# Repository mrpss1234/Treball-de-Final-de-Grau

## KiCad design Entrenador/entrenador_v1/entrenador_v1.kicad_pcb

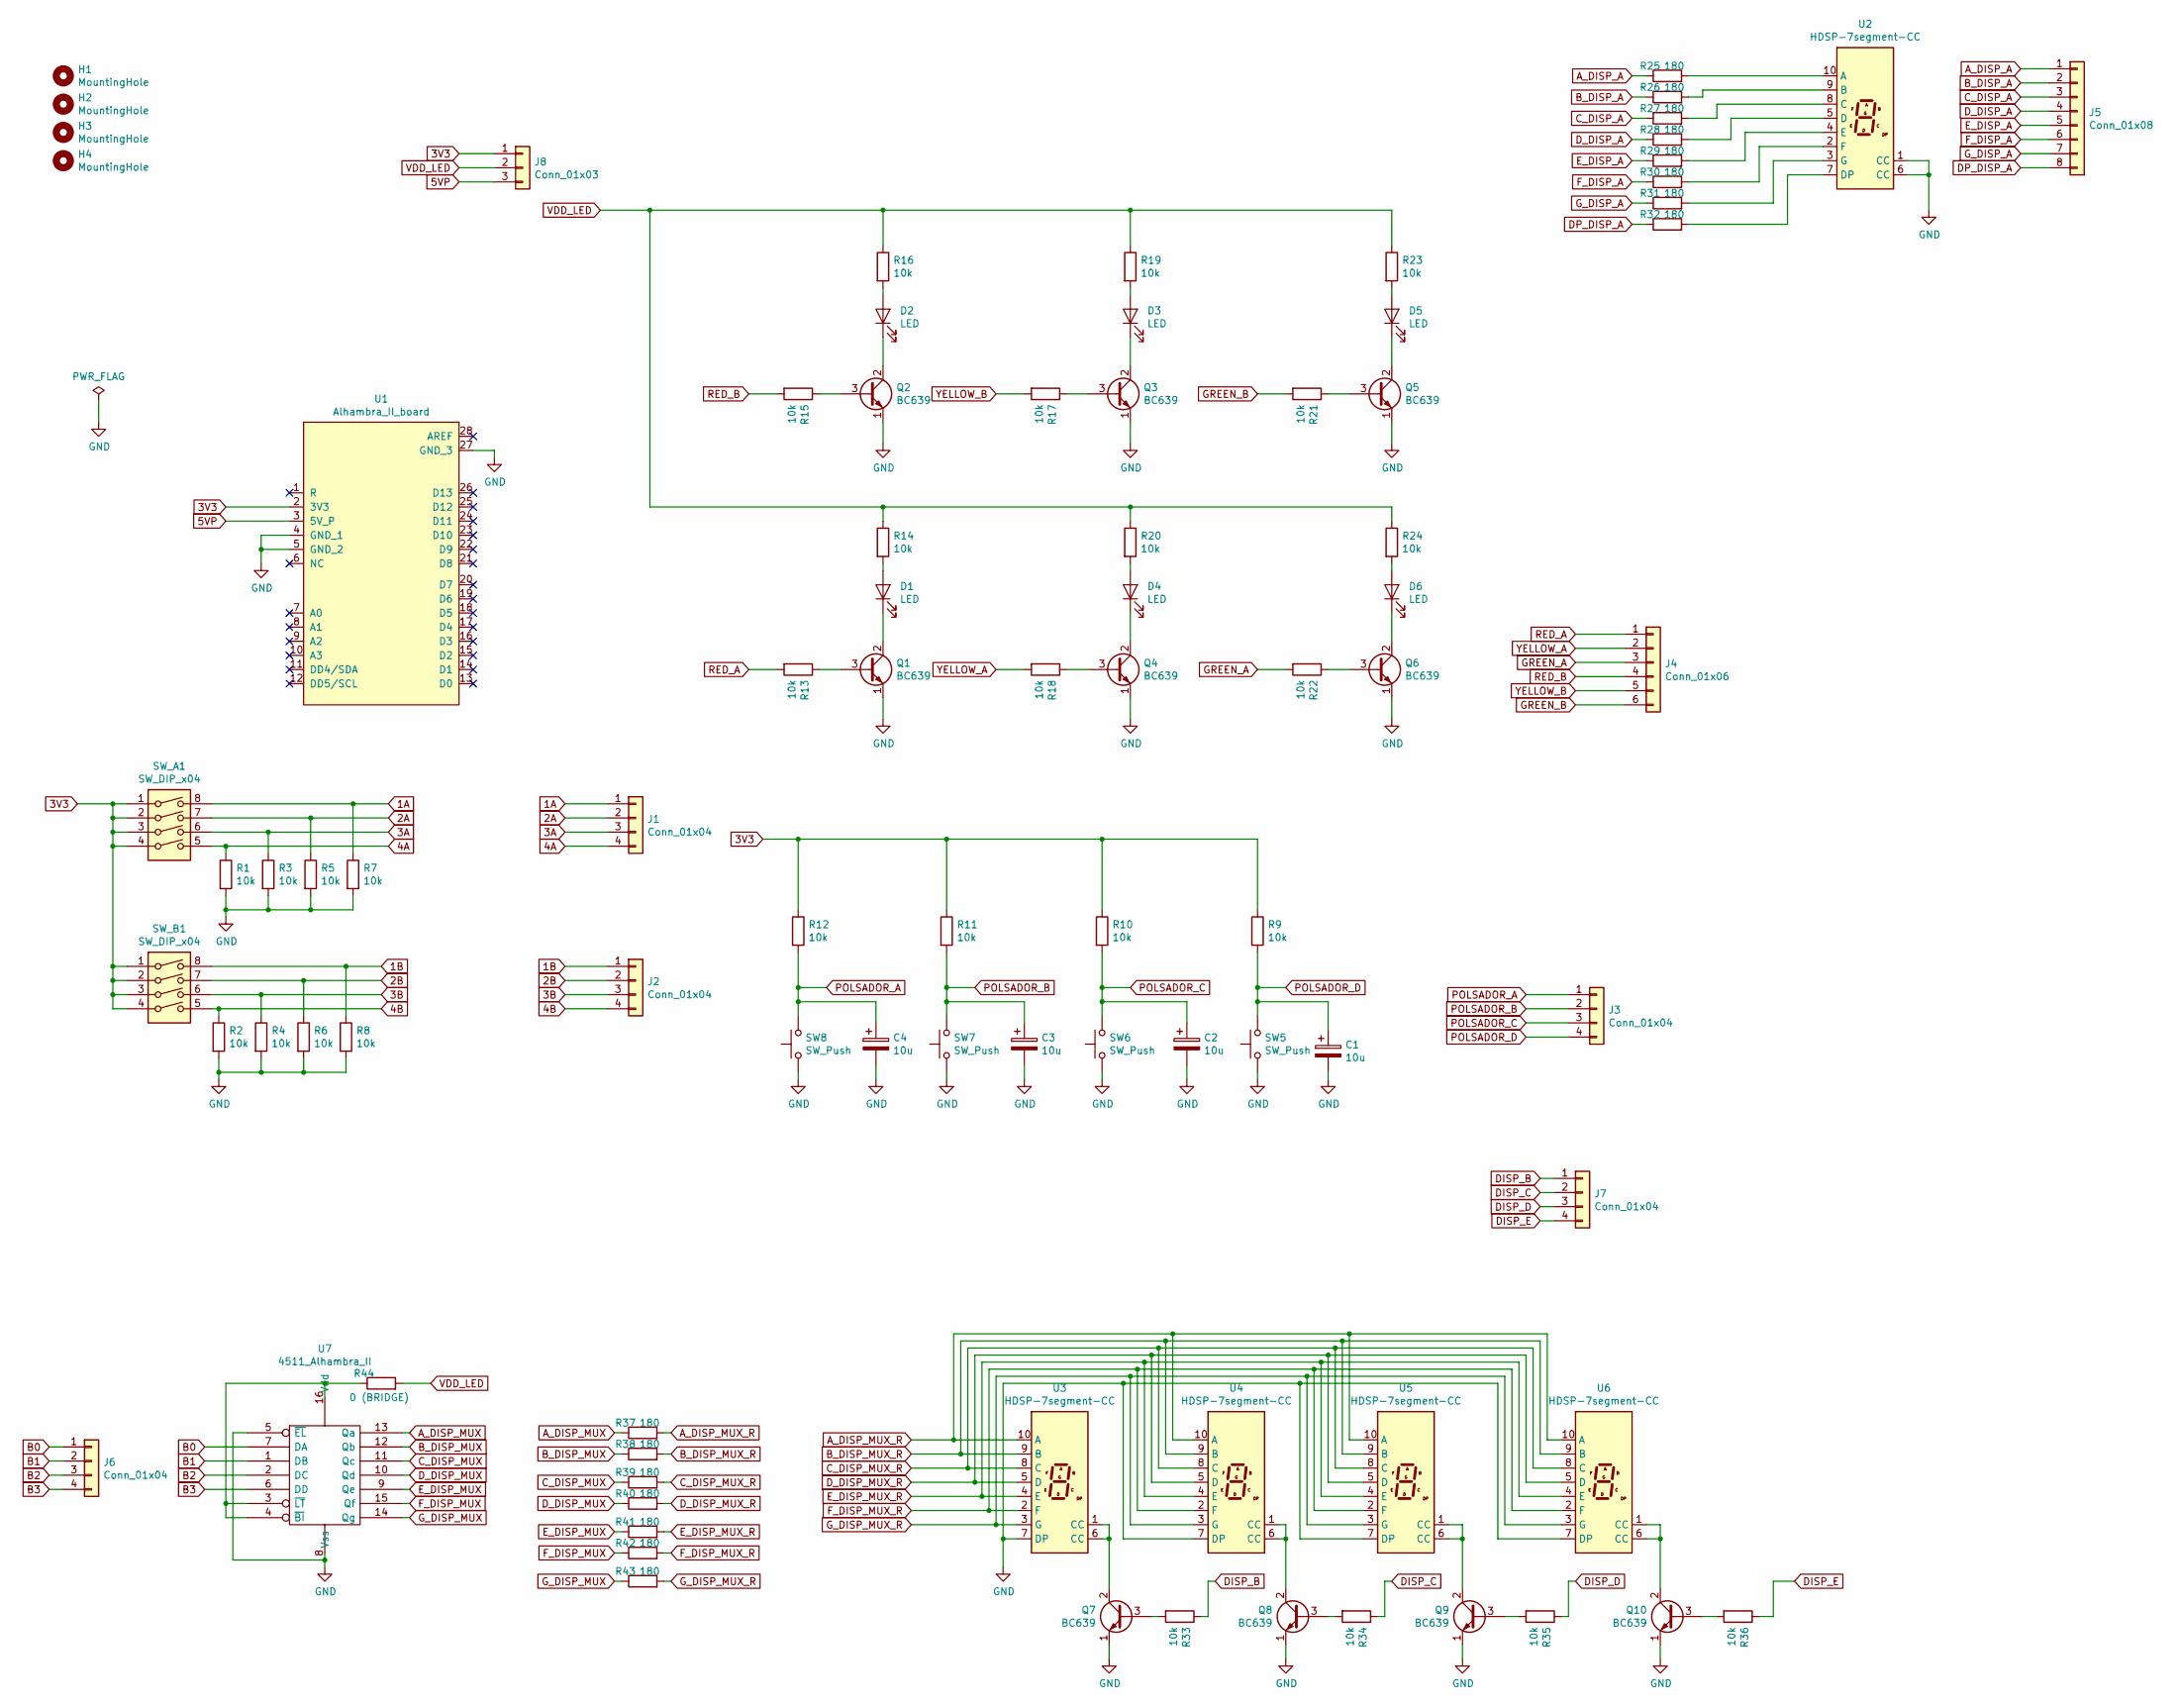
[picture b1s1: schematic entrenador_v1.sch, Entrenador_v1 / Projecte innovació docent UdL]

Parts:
C1, C2, C3, C4: 10u; CP_Radial_D5.0mm_P2.50mm
D1, D2, D3, D4, D5, D6: LED; LED_D3.0mm_Alhambra_II
H1, H2, H3, H4: MountingHole; MountingHole_4mm
J1, J2, J3, J6, J7: Conn_01x04; PinSocket_1x04_P2.54mm_Vertical_Alhambra_II
J4: Conn_01x06; PinSocket_1x06_P2.54mm_Vertical_Alhambra_II
J5: Conn_01x08; PinSocket_1x08_P2.54mm_Vertical_Alhambra_II
J8: Conn_01x03; PinHeader_1x03_P2.54mm_Vertical_Alhambra_II
Q1, Q2, Q3, Q4, Q5, Q6, Q7, Q8, Q9, Q10: BC639; TO-92L_Inline_Wide_Alhambra_II
R1, R2, R3, R4, R5, R6, R7, R8, R9, R10, R11, R12, R13, R14, R15, R16, R17, R18, R19, R20, R21, R22, R23, R24, R33, R34, R35, R36: 10k; R_Axial_Alhambra_II
R25, R26, R27, R28, R29, R30, R31, R32, R37, R38, R39, R40, R41, R42, R43: 180; R_Axial_Alhambra_II
R44: 0 (BRIDGE); R_Axial_Alhambra_II
SW5, SW6, SW7, SW8: SW_Push; PUSH_Button_Alhambra_II
SW_A1: SW_DIP_x04; DIP_SWITCH_4P_Alhambra_II
SW_B1: SW_DIP_x04; DIP_SWITCH_4P_Alhambra_II
U1: Alhambra_II_board; Alhambra_II_UdL_v2
U2, U3, U4, U5, U6: HDSP-7segment-CC; HDSP_7seg_Alhambra_II
U7: 4511_Alhambra_II; DIP-16_W7.62mm_Socket_LongPads

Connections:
1A: J1.1, R7.1, SW_A1.8
1B: J2.1, R8.1, SW_B1.8
2A: J1.2, R5.1, SW_A1.7
2B: J2.2, R6.1, SW_B1.7
3A: J1.3, R3.1, SW_A1.6
3B: J2.3, R4.1, SW_B1.6
3V3: J8.1, R9.1, R10.1, R11.1, R12.1, SW_A1.1, SW_A1.2, SW_A1.3, SW_A1.4, SW_B1.1, SW_B1.2, SW_B1.3, SW_B1.4, U1.2 (3V3)
4A: J1.4, R1.1, SW_A1.5
4B: J2.4, R2.1, SW_B1.5
5VP: J8.3, U1.3 (5V_P)
A_DISP_A: J5.1, R25.1
A_DISP_MUX: R37.1, U7.13 (Qa)
A_DISP_MUX_R: R37.2, U3.10 (A), U4.10 (A), U5.10 (A), U6.10 (A)
B0: J6.1, U7.7 (DA)
B1: J6.2, U7.1 (DB)
B2: J6.3, U7.2 (DC)
B3: J6.4, U7.6 (DD)
B_DISP_A: J5.2, R26.1
B_DISP_MUX: R38.1, U7.12 (Qb)
B_DISP_MUX_R: R38.2, U3.9 (B), U4.9 (B), U5.9 (B), U6.9 (B)
C_DISP_A: J5.3, R27.1
C_DISP_MUX: R39.1, U7.11 (Qc)
C_DISP_MUX_R: R39.2, U3.8 (C), U4.8 (C), U5.8 (C), U6.8 (C)
DISP_B: J7.1, R33.1
DISP_C: J7.2, R34.1
DISP_D: J7.3, R35.1
DISP_E: J7.4, R36.1
DP_DISP_A: J5.8, R32.1
D_DISP_A: J5.4, R28.1
D_DISP_MUX: R40.1, U7.10 (Qd)
D_DISP_MUX_R: R40.2, U3.5 (D), U4.5 (D), U5.5 (D), U6.5 (D)
E_DISP_A: J5.5, R29.1
E_DISP_MUX: R41.1, U7.9 (Qe)
E_DISP_MUX_R: R41.2, U3.4 (E), U4.4 (E), U5.4 (E), U6.4 (E)
F_DISP_A: J5.6, R30.1
F_DISP_MUX: R42.1, U7.15 (Qf)
F_DISP_MUX_R: R42.2, U3.2 (F), U4.2 (F), U5.2 (F), U6.2 (F)
GND: C1.2, C2.2, C3.2, C4.2, Q1.1 (E), Q2.1 (E), Q3.1 (E), Q4.1 (E), Q5.1 (E), Q6.1 (E), Q7.1 (E), Q8.1 (E), Q9.1 (E), Q10.1 (E), R1.2, R2.2, R3.2, R4.2, R5.2, R6.2, R7.2, R8.2, SW5.2, SW6.2, SW7.2, SW8.2, U1.4 (GND_1), U1.5 (GND_2), U1.27 (GND_3), U2.1 (CC), U2.6 (CC), U3.7 (DP), U4.7 (DP), U5.7 (DP), U6.7 (DP), U7.5 (~EL), U7.8 (Vss)
GREEN_A: J4.3, R22.2
GREEN_B: J4.6, R21.2
G_DISP_A: J5.7, R31.1
G_DISP_MUX: R43.1, U7.14 (Qg)
G_DISP_MUX_R: R43.2, U3.3 (G), U4.3 (G), U5.3 (G), U6.3 (G)
unnamed: D1.1 (K), Q1.2 (C)
unnamed: D1.2 (A), R14.2
unnamed: D2.1 (K), Q2.2 (C)
unnamed: D2.2 (A), R16.2
unnamed: D3.1 (K), Q3.2 (C)
unnamed: D3.2 (A), R19.2
unnamed: D4.1 (K), Q4.2 (C)
unnamed: D4.2 (A), R20.2
unnamed: D5.1 (K), Q5.2 (C)
unnamed: D5.2 (A), R23.2
unnamed: D6.1 (K), Q6.2 (C)
unnamed: D6.2 (A), R24.2
unnamed: Q1.3 (B), R13.1
unnamed: Q2.3 (B), R15.1
unnamed: Q3.3 (B), R17.1
unnamed: Q4.3 (B), R18.1
unnamed: Q5.3 (B), R21.1
unnamed: Q6.3 (B), R22.1
unnamed: Q7.2 (C), U3.1 (CC), U3.6 (CC)
unnamed: Q7.3 (B), R33.2
unnamed: Q8.2 (C), U4.1 (CC), U4.6 (CC)
unnamed: Q8.3 (B), R34.2
unnamed: Q9.2 (C), U5.1 (CC), U5.6 (CC)
unnamed: Q9.3 (B), R35.2
unnamed: Q10.2 (C), U6.1 (CC), U6.6 (CC)
unnamed: Q10.3 (B), R36.2
unnamed: R25.2, U2.10 (A)
unnamed: R26.2, U2.9 (B)
unnamed: R27.2, U2.8 (C)
unnamed: R28.2, U2.5 (D)
unnamed: R29.2, U2.4 (E)
unnamed: R30.2, U2.2 (F)
unnamed: R31.2, U2.3 (G)
unnamed: R32.2, U2.7 (DP)
unnamed: R44.1, U7.3 (~LT), U7.4 (~BI), U7.16 (Vdd)
POLSADOR_A: C4.1, J3.1, R12.2, SW8.1
POLSADOR_B: C3.1, J3.2, R11.2, SW7.1
POLSADOR_C: C2.1, J3.3, R10.2, SW6.1
POLSADOR_D: C1.1, J3.4, R9.2, SW5.1
RED_A: J4.1, R13.2
RED_B: J4.4, R15.2
VDD_LED: J8.2, R14.1, R16.1, R19.1, R20.1, R23.1, R24.1, R44.2
YELLOW_A: J4.2, R18.2
YELLOW_B: J4.5, R17.2

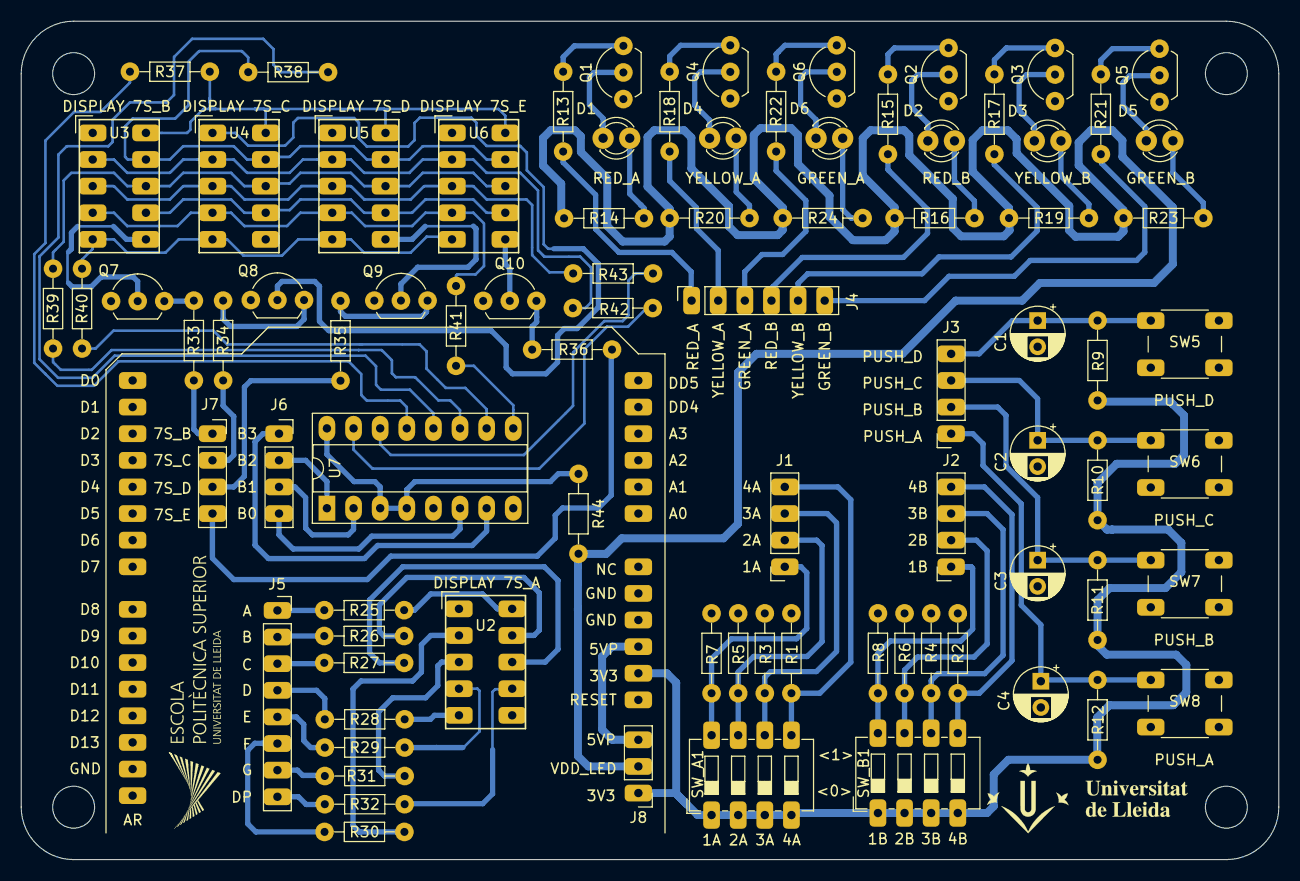
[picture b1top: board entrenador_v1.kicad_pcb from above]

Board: 2 copper layers, 120.0 x 80.0 mm, 89 parts (0 on the bottom side), 87 nets.

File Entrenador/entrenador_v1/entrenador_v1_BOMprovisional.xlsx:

Id | Designator | Package | Quantity | Designation | Supplier and ref
1 | D6,D5,D4,D3,D2,D1 | LED_D3.0mm_Alhambra_II | 6 | LED
2 | Q6,Q5,Q4,Q3,Q2,Q1,Q10,Q9,Q8,Q7 | TO-92L_Inline_Wide_Alhambra_II | 10 | BC639
3 | R36,R35,R34,R33,R1,R2,R3,R4,R5,R6,R7,R8,R9,R10,R11,R12,R13,R14,R15,R16,R17,R18,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 | R_Axial_Alhambra_II | 28 | 10k
4 | R25,R26,R27,R28,R29,R30,R31,R32,R37,R38,R39,R41,R42,R43,R40 | R_Axial_Alhambra_II | 15 | 180
5 | R44 | R_Axial_Alhambra_II | 1 | 0 (BRIDGE)
6 | U7 | DIP-16_W7.62mm_Socket_LongPads | 1 | 4511_Alhambra_II
7 | SW6,SW8,SW7,SW5 | PUSH_Button_Alhambra_II | 4 | SW_Push
8 | J2,J1,J3,J6,J7 | PinSocket_1x04_P2.54mm_Vertical_Alhambra_II | 5 | Conn_01x04
9 | SW_A1,SW_B1 | DIP_SWITCH_4P_Alhambra_II | 2 | SW_DIP_x04
10 | C1,C2,C3,C4 | CP_Radial_D5.0mm_P2.50mm | 4 | 10u
11 | J4 | PinSocket_1x06_P2.54mm_Vertical_Alhambra_II | 1 | Conn_01x06
12 | U3,U5,U2,U6,U4 | HDSP_7seg_Alhambra_II | 5 | HDSP-7segment-CC
13 | J5 | PinSocket_1x08_P2.54mm_Vertical_Alhambra_II | 1 | Conn_01x08
14 | J8 | PinHeader_1x03_P2.54mm_Vertical_Alhambra_II | 1 | Conn_01x03
15 | H1,H2,H3,H4 | MountingHole_4mm | 4 | MountingHole
16 | G*** | logoUdLEPS | 1 | LOGO
17 | G*** | logoUdLEPS_nou | 1 | LOGO
18 | U1 | Alhambra_II_UdL_v2 | 1 | Alhambra_II_board

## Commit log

2020-06-15 Create md
2020-06-30 Create Repositori
